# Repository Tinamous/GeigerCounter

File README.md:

# GeigerCounter
Particle Photon based Geiger counter.

Based on MightyOhm.com Geiger Counter (V1.0).

Connect Photon pin D0 to pulse output of Geiger (Pin 2 middle pin of Pulse connector).

Remove batteries and connect 3v3 and Gnd of Photon to 1 & 3 of Pulse connector.
or
Leave batteris in and connect Gnd of Photon to Pin 3 (GND) of Pulse connector. Do not connect 3v3.

Optional: Add red LED to Pin D1 via a 1K resistor and other LED pin to GND.

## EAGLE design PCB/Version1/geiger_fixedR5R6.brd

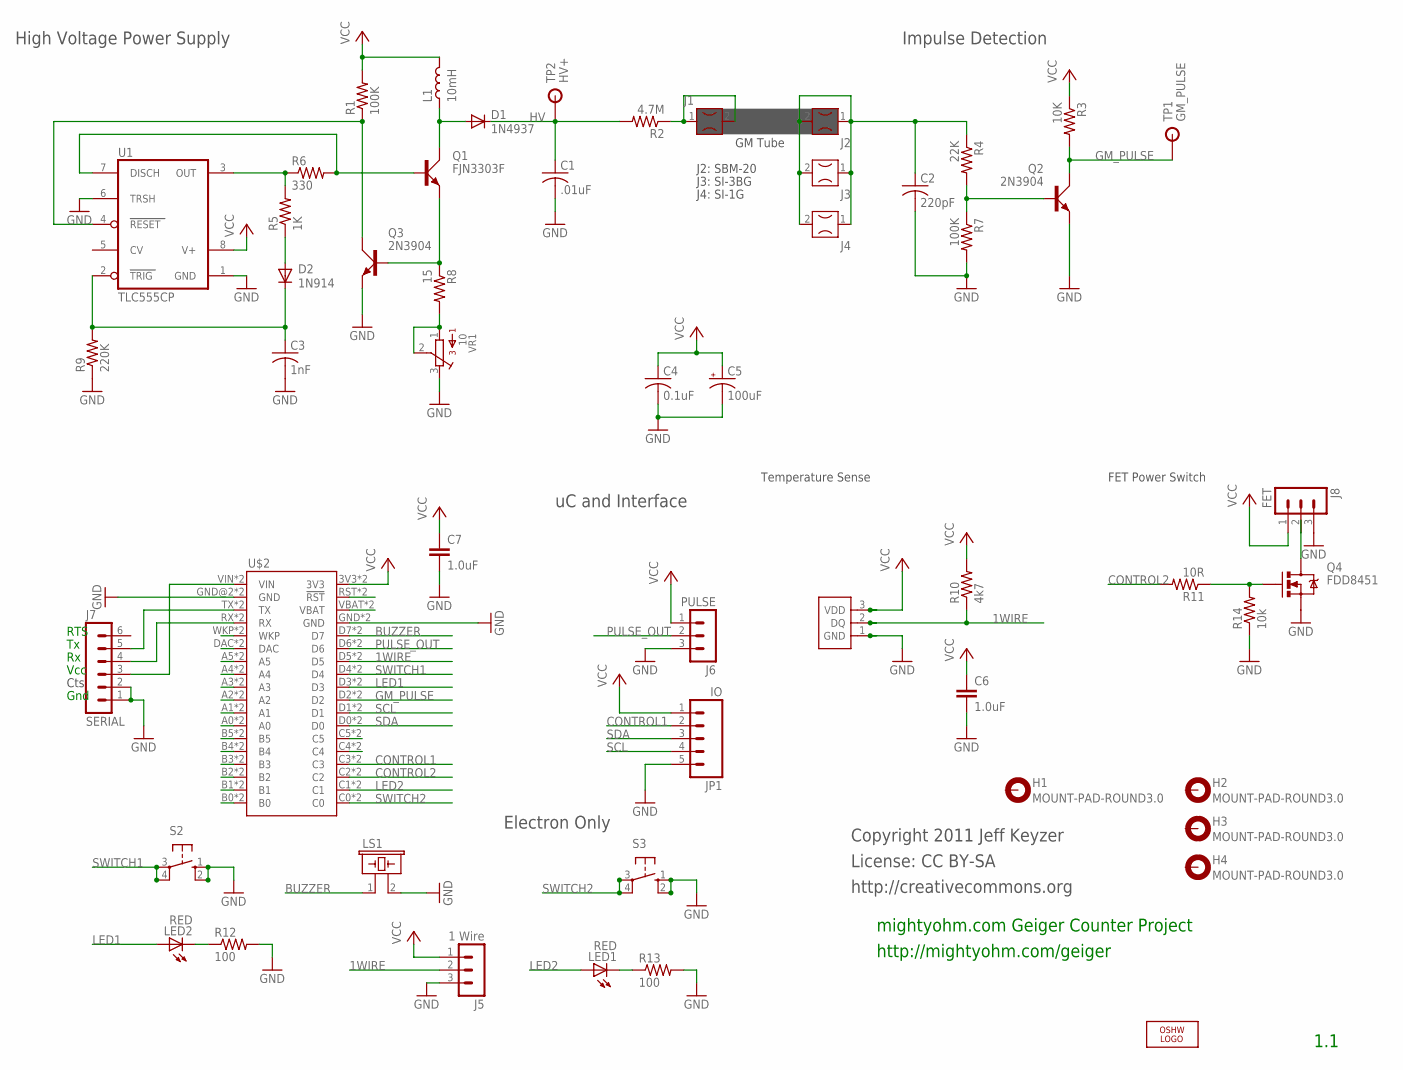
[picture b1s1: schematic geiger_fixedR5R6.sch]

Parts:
C1: .01uF; C102-043X133
C2: 220pF; C050-030X075
C3: 1nF; C050-025X075
C4: 0.1uF; C025-025X050
C5: 100uF; E2,5-6
C6, C7: 1.0uF; 0805-CAP
D1: 1N4937; DO41-10
D2: 1N914; DO35-7
H1, H2, H3, H4: MOUNT-PAD-ROUND3.0; 3,0-PAD
J1, J2, J3, J4: FUSECLIPPCMOUNT; FUSECLIP_PCMOUNT
J5: 1 Wire; MA03-1
J6: PULSE; MA03-1
J7: SERIAL; MA06-1
J8: FET; MA03-1
JP1: IO; 1X05
L1: 10mH; ELC09D
LED1, LED2: RED; LED5MM
LOGO1: OSHW_LOGO_FILLX0200-NT; OSHW_FILLX200_NOTEXT
LS1: PIEZO17MM; PS1740P02E
Q1: FJN3303F; TO92C
Q2, Q3: 2N3904; TO92D
Q4: FDD8451; DPAK
R1, R7: 100K; 0207/10
R2: 4.7M; 0207/10
R3: 10K; 0207/10
R4: 22K; 0207/10
R5: 1K; 0207/10
R6: 330; 0207/10
R8: 15; 0207/10
R9: 220K; 0207/10
R10: 4k7; R0805
R11: 10R; R0805
R12, R13: 100; R0805
R14: 10k; R0805
S1: DB18B20+; TO-92-TRIANGLE
S2, S3: 10-XX; B3F-10XX
TP1: GM_PULSE; TP_PTH
TP2: HV+; TP_PTH
U1: TLC555CP; DIL08
U$2: ELECTRONDUALNAMED; ELECTRON_SIMPLE_SILK_NAMES_DUAL
VR1: 10; 3386P

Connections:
1WIRE: J5.2, R10.1, S1.2 (DQ), U$2.D5, U$2.D5_1 (D5)
BUZZER: LS1.1, U$2.D7, U$2.D7_1 (D7)
CONTROL1: JP1.2, U$2.C3, U$2.C3_1 (C3)
CONTROL2: R11.2, U$2.C2, U$2.C2_1 (C2)
GM_PULSE: Q2.C, R3.2, TP1.P$1, U$2.D2, U$2.D2_1 (D2)
GND: C1.2, C2.2, C3.2, C4.2, C5.-, C6.2, C7.2, J5.3, J6.3, J7.1, J7.2, J8.3, JP1.5, LS1.2, Q2.E, Q3.E, Q4.3 (S), R7.2, R9.1, R12.2, R13.2, R14.1, S1.1 (GND), S2.1 (S), S2.2 (S1), S3.1 (S), S3.2 (S1), U1.1 (GND), U1.6 (TRSH), U$2.GND, U$2.GND@2 (GND), U$2.GND_1 (GND), U$2.GND_1B (GND), VR1.3
HV: C1.1, D1.C, R2.2, TP2.P$1
LED1: LED2.A, U$2.D3, U$2.D3_1 (D3)
LED2: LED1.A, U$2.C1, U$2.C1_1 (C1)
unnamed: D2.A, R5.1
unnamed: U$2.RST (!RST), U$2.RST_1 (!RST)
unnamed: Q3.C, R1.1, U1.4 (RESET)
unnamed: U$2.VBAT, U$2.VBATT_1 (VBAT)
unnamed: U$2.C5, U$2.C5_1 (C5)
unnamed: J7.3, U$2.VIN, U$2.VIN_1B (VIN)
unnamed: J7.5, U$2.TX, U$2.TX_1 (TX)
unnamed: Q1.B, R6.2, U1.7 (DISCH)
unnamed: C3.1, D2.C, R9.2, U1.2 (TRIG)
unnamed: R5.2, R6.1, U1.3 (OUT)
unnamed: Q1.E, Q3.B, R8.1
unnamed: D1.A, L1.1, Q1.C
unnamed: J7.4, U$2.RX, U$2.RX_1 (RX)
unnamed: Q2.B, R4.2, R7.1
unnamed: J1.1, J1.2, R2.1
unnamed: U$2.WKP, U$2.WKP_1 (WKP)
unnamed: U$2.DAC, U$2.DAC_1 (DAC)
unnamed: LED2.K (C), R12.1
unnamed: U$2.A5, U$2.A5_1 (A5)
unnamed: U$2.A4, U$2.A4_1 (A4)
unnamed: LED1.K (C), R13.1
unnamed: U$2.A3, U$2.A3_1 (A3)
unnamed: R8.2, VR1.1, VR1.2
unnamed: U$2.A2, U$2.A2_1 (A2)
unnamed: U$2.A1, U$2.A1_1 (A1)
unnamed: U$2.A0, U$2.A0_1 (A0)
unnamed: U$2.B5, U$2.B5_1 (B5)
unnamed: U$2.B4, U$2.B4_1 (B4)
unnamed: U$2.B3, U$2.B3_1 (B3)
unnamed: U$2.B2, U$2.B2_1 (B2)
unnamed: U$2.B1, U$2.B1_1 (B1)
unnamed: U$2.B0, U$2.B0_1 (B0)
unnamed: U$2.C4, U$2.C4_1 (C4)
unnamed: Q4.1 (G), R11.1, R14.2
unnamed: J8.2, Q4.4 (D)
unnamed: C2.1, J2.1, J2.2, J3.1, J3.2, J4.1, J4.2, R4.1
PULSE_OUT: J6.2, U$2.D6, U$2.D6_1 (D6)
SCL: JP1.4, U$2.D1, U$2.D1_1 (D1)
SDA: JP1.3, U$2.D0, U$2.D0_1 (D0)
SWITCH1: S2.3, S2.4 (P1), U$2.D4, U$2.D4_1 (D4)
SWITCH2: S3.3, S3.4 (P1), U$2.C0, U$2.C0_1 (C0)
VCC: C4.1, C5.+, C6.1, C7.1, J5.1, J6.1, J8.1, JP1.1, L1.2, R1.2, R3.1, R10.2, S1.3 (VDD), U1.8 (V+), U$2.3V3, U$2.3V3_1 (3V3)

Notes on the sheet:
1.1
mightyohm.com Geiger Counter Project
GM Tube
License: CC BY-SA
http://creativecommons.org
http://mightyohm.com/geiger
Copyright 2011 Jeff Keyzer
J2: SBM-20
J3: SI-3BG
J4: SI-1G
High Voltage Power Supply
Impulse Detection
uC and Interface
Cts
Gnd
Electron Only
RTS
Vcc
Temperature Sense
FET Power Switch

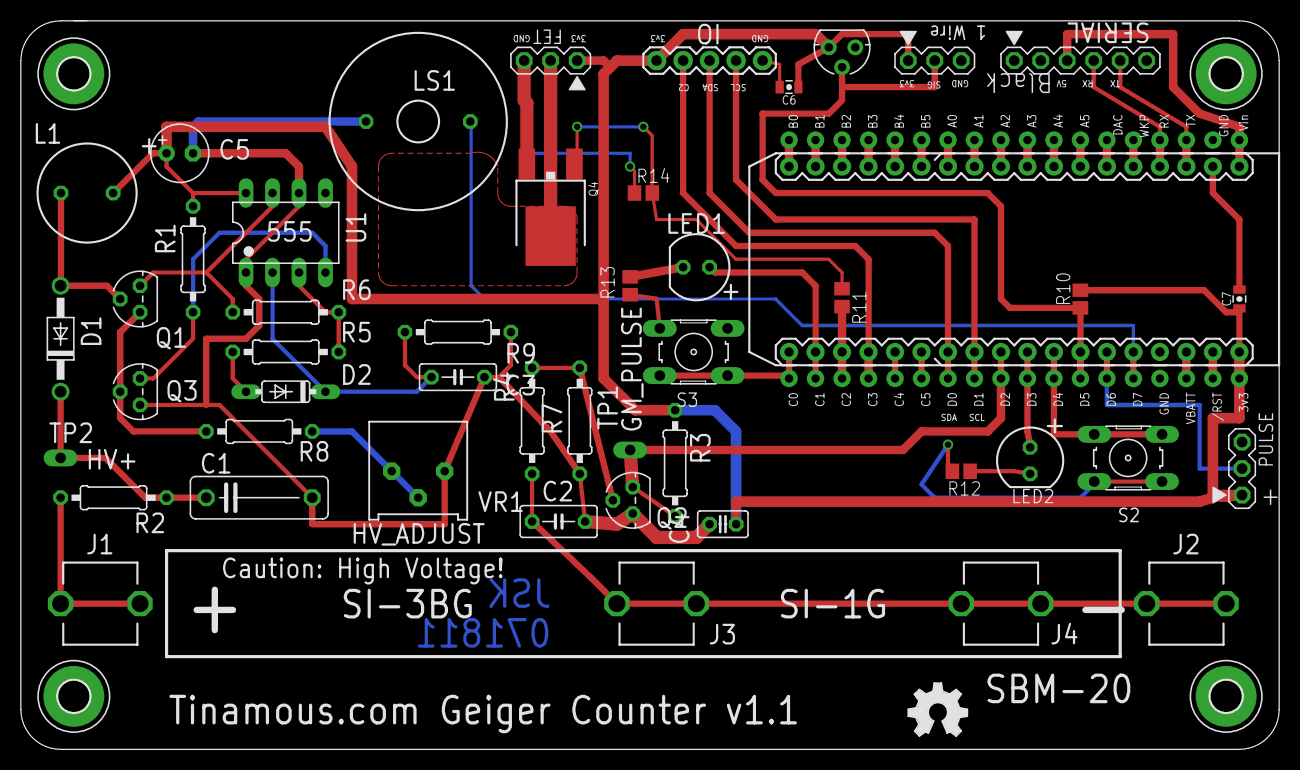
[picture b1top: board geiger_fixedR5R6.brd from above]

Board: 2 copper layers, 120.7 x 69.8 mm, 53 parts (0 on the bottom side), 51 nets.

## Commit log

2015-12-07 Added "Version 1" of IoT Gieger Counter using Particle Electron.
    As send to OSHPark for fab.
    Adaptation of MightyOhm.com Geiger Counter V1.0

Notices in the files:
parts and their libraries:
SparkFun-Connectors: Licensing: Creative Commons ShareAlike 4.0 International - https://creativecommons.org/licenses/by-sa/4.0
